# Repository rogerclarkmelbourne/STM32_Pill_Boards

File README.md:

# STM32_Pill_Boards

This repo contains a KiCad conversion of the STM32STAMP board and also two new BluePill F4 boards designed by @racemaniac and @Squonk42

My previous attemps have been deleted.

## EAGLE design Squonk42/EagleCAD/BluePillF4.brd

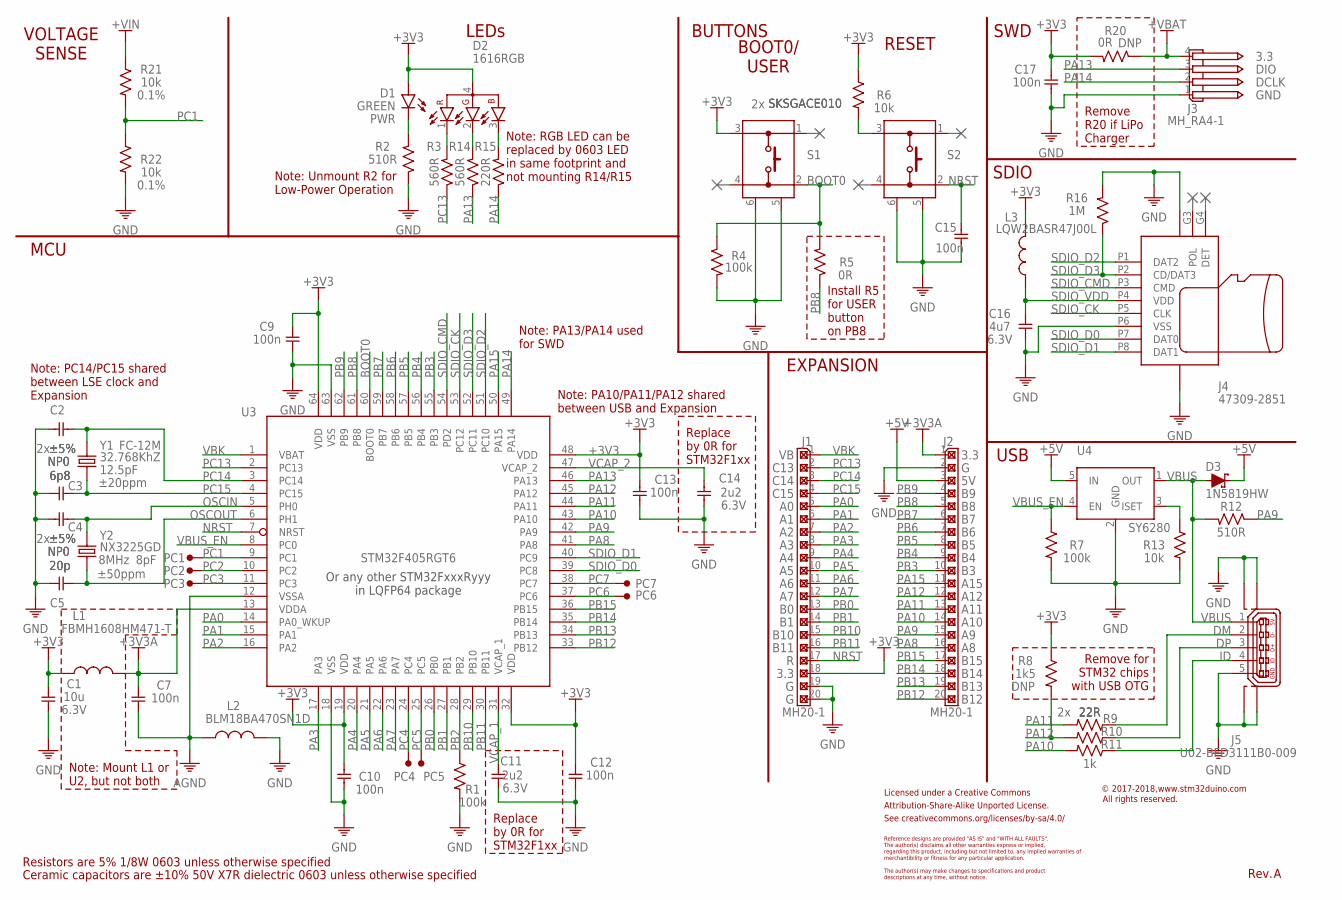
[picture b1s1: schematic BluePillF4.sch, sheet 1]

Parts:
C1: 10u; C0603; PARTNO C0603_10u_X7R_10%_CER_6V3
C2, C3: 6p8; C0603; PARTNO C0603_6p8_NP0_5%_CER_50V
C4, C5: 20p; C0603; PARTNO C0603_20p_NP0_5%_CER_50V
C7, C9, C10, C12, C13, C15, C17: 100n; C0603; PARTNO C0603_100n_X7R_10%_CER_50V
C11, C14: 2u2; C0603; PARTNO C0603_2u2_X7R_10%_CER_6V3
C16: 4u7; C0603; PARTNO C0603_4u7_X7R_10%_CER_6V3
D1: GREEN; LED0603; PARTNO LED0603-GREEN
D2: 1616RGB; PARTNO LED1616-RGB
D3: 1N5819HW; SOD-123
J1, J2: MH20-1; MH20-1-0.1; PARTNO MH20-1-0.1
J3: MH_RA4-1; MH_RA4-1-0.1; PARTNO MH_RA4-1-0.1
J4: 47309-2851
J5: U02-BFD3111B0-009; PARTNO U02-BFD3111B0-009
L1: FBMH1608HM471-T; FB0603; PARTNO FBMH1608HM471-T
L2: BLM18BA470SN1D; FB0603; PARTNO BLM18BA470SN1D
L3: LQW2BASR47J00L; FB0805; PARTNO LQW2BASR47J00L
LOGO1: CC-BY-SA_LOGO
PC1, PC2, PC3, PC4, PC5, PC6, PC7: TEST_PAD
R1, R4, R7: 100k; R0603; PARTNO R0603_100k_5%_125mW
R2, R12: 510R; R0603; PARTNO R0603_510R_5%_125mW
R3, R14: 560R; R0603; PARTNO R0603_510R_5%_125mW
R5, R20: 0R; R0603; PARTNO R0603_510R_5%_125mW
R6, R13: 10k; R0603; PARTNO R0603_10k_5%_125mW
R8: 1k5; R0603; PARTNO R0603_1k5_5%_125mW
R9, R10: 22R; R0603; PARTNO R0603_22R_5%_125mW
R11: 1k; R0603; PARTNO R0603_1k_5%_125mW
R15: 220R; R0603; PARTNO R0603_510R_5%_125mW
R16: 1M; R0603; PARTNO R0603_1M_5%_125mW
R21, R22: 10k; R0603; PARTNO R0603_10k_0.1%_125mW
S1, S2: SKSGACE010
U3: STM32F405RGT6; LQFP64
U4: SY6280; SOT23-5
Y1: FC-12M; PARTNO FC-12M 32.7680KA-A3
Y2: NX3225GD; CRYSTAL_32X25_2P; PARTNO NX3225GD-8MHZ-STD-CRA-3

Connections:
+3V3: C1.1, C9.2, C10.2, C12.1, C13.1, C17.2, D1.2 (A), D2.4 (A), J1.18, L1.1, L3.2, R6.1, R8.1, R20.2, S1.3 (A), U3.19 (VDD), U3.32 (VDD), U3.48 (VDD), U3.64 (VDD); also elsewhere on the board
+3V3A: C7.2, J2.1, L1.2, U3.13 (VDDA); also elsewhere on the board
+5V: D3.C, J2.3, U4.5 (IN); also elsewhere on the board
+VBAT: J3.4, R20.1; also elsewhere on the board
+VIN: R21.1; also elsewhere on the board
AGND: C7.1, L2.1, U3.12 (VSSA); also elsewhere on the board
BOOT0: R4.1, R5.2, S1.2 (B), U3.60 (BOOT0)
D1: D1.1 (C), R2.2
D2_B: D2.3 (CB), R15.2
D2_G: D2.2 (CG), R14.2
D2_R: D2.1 (CR), R3.2
DM: J5.2, R9.1
DP: J5.3, R10.1
GND: C1.2, C2.2, C3.2, C4.2, C5.2, C9.1, C10.1, C11.1, C12.2, C13.2, C14.1, C15.1, C16.1, C17.1, J1.19, J1.20, J2.2, J3.1, J4.G1 (GND), J4.G2 (GND), J4.P6 (VSS), J5.5, J5.S$1 (M0), J5.S$2 (M1), J5.S$3 (M2), J5.S$4 (M3), L2.2, R1.2, R2.1, R4.2, R7.2, R13.2, R16.2, R22.2, S1.5, S1.6, S2.5, S2.6, U3.18 (VSS), U3.63 (VSS), U4.2 (GND); also elsewhere on the board
ID: J5.4, R11.1
ISET: R13.1, U4.3 (ISET)
NRST: C15.2, J1.17, S2.2 (B), U3.7 (NRST)
OSCIN: C4.1, U3.5 (PH0), Y2.2
OSCOUT: C5.1, U3.6 (PH1), Y2.1
PA0: J1.5, U3.14 (PA0_WKUP)
PA1: J1.6, U3.15 (PA1)
PA2: J1.7, U3.16 (PA2)
PA3: J1.8, U3.17 (PA3)
PA4: J1.9, U3.20 (PA4)
PA5: J1.10, U3.21 (PA5)
PA6: J1.11, U3.22 (PA6)
PA7: J1.12, U3.23 (PA7)
PA8: J2.16, U3.41 (PA8)
PA9: J2.15, R12.1, U3.42 (PA9)
PA10: J2.14, R11.2, U3.43 (PA10)
PA11: J2.13, R9.2, U3.44 (PA11)
PA12: J2.12, R8.2, R10.2, U3.45 (PA12)
PA13: J3.3, R14.1, U3.46 (PA13)
PA14: J3.2, R15.1, U3.49 (PA14)
PA15: J2.11, U3.50 (PA15)
PB0: J1.13, U3.26 (PB0)
PB1: J1.14, U3.27 (PB1)
PB2: R1.1, U3.28 (PB2)
PB3: J2.10, U3.55 (PB3)
PB4: J2.9, U3.56 (PB4)
PB5: J2.8, U3.57 (PB5)
PB6: J2.7, U3.58 (PB6)
PB7: J2.6, U3.59 (PB7)
PB8: J2.5, R5.1, U3.61 (PB8)
PB9: J2.4, U3.62 (PB9)
PB10: J1.15, U3.29 (PB10)
PB11: J1.16, U3.30 (PB11)
PB12: J2.20, U3.33 (PB12)
PB13: J2.19, U3.34 (PB13)
PB14: J2.18, U3.35 (PB14)
PB15: J2.17, U3.36 (PB15)
PC1: PC1.1, R21.2, R22.1, U3.9 (PC1)
PC2: PC2.1, U3.10 (PC2)
PC3: PC3.1, U3.11 (PC3)
PC4: PC4.1, U3.24 (PC4)
PC5: PC5.1, U3.25 (PC5)
PC6: PC6.1, U3.37 (PC6)
PC7: PC7.1, U3.38 (PC7)
PC13: J1.2, R3.1, U3.2 (PC13)
PC14: C2.1, J1.3, U3.3 (PC14), Y1.2
PC15: C3.1, J1.4, U3.4 (PC15), Y1.1
R6: R6.2, S2.3 (A)
SDIO_CK: J4.P5 (CLK), U3.53 (PC12)
SDIO_CMD: J4.P3 (CMD), U3.54 (PD2)
SDIO_D0: J4.P7 (DAT0), U3.39 (PC8)
SDIO_D1: J4.P8 (DAT1), U3.40 (PC9)
SDIO_D2: J4.P1 (DAT2), U3.51 (PC10)
SDIO_D3: J4.P2 (CD/DAT3), R16.1, U3.52 (PC11)
SDIO_VDD: C16.2, J4.P4 (VDD), L3.1
VBK: J1.1, U3.1 (VBAT)
VBUS: D3.A, J5.1, R12.2, U4.1 (OUT)
VBUS_EN: R7.1, U3.8 (PC0), U4.4 (EN)
VCAP_1: C11.2, U3.31 (VCAP_1)
VCAP_2: C14.2, U3.47 (VCAP_2)

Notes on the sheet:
Licensed under a Creative Commons
Attribution-Share-Alike Unported License.
See creativecommons.org/licenses/by-sa/4.0/
Reference designs are provided "AS IS" and "WITH ALL FAULTS".
regarding this product, including but not limited to, any implied warranties of
The author(s) may make changes to specifications and product
The author(s) disclaims all other warranties express or implied,
merchantibility or fitness for any particular application.
descriptions at any time, without notice.
All rights reserved.
Rev.
Ceramic capacitors are ±10% 50V X7R dielectric 0603 unless otherwise specified
Resistors are 5% 1/8W 0603 unless otherwise specified
© 2017-2018,
Remove for STM32 chips with USB OTG
Replace by 0R for STM32F1xx
RESET
BOOT0/ USER
SWD
USB
LEDs
Install R5 for USER button on PB8
PWR
SDIO
BUTTONS
EXPANSION
MCU
Note: PC14/PC15 shared between LSE clock and Expansion
Note: PA10/PA11/PA12 shared between USB and Expansion
Note: PA13/PA14 used for SWD
DIO
DCLK
3.3
GND
C13
C14
C15
B10
B11
A15

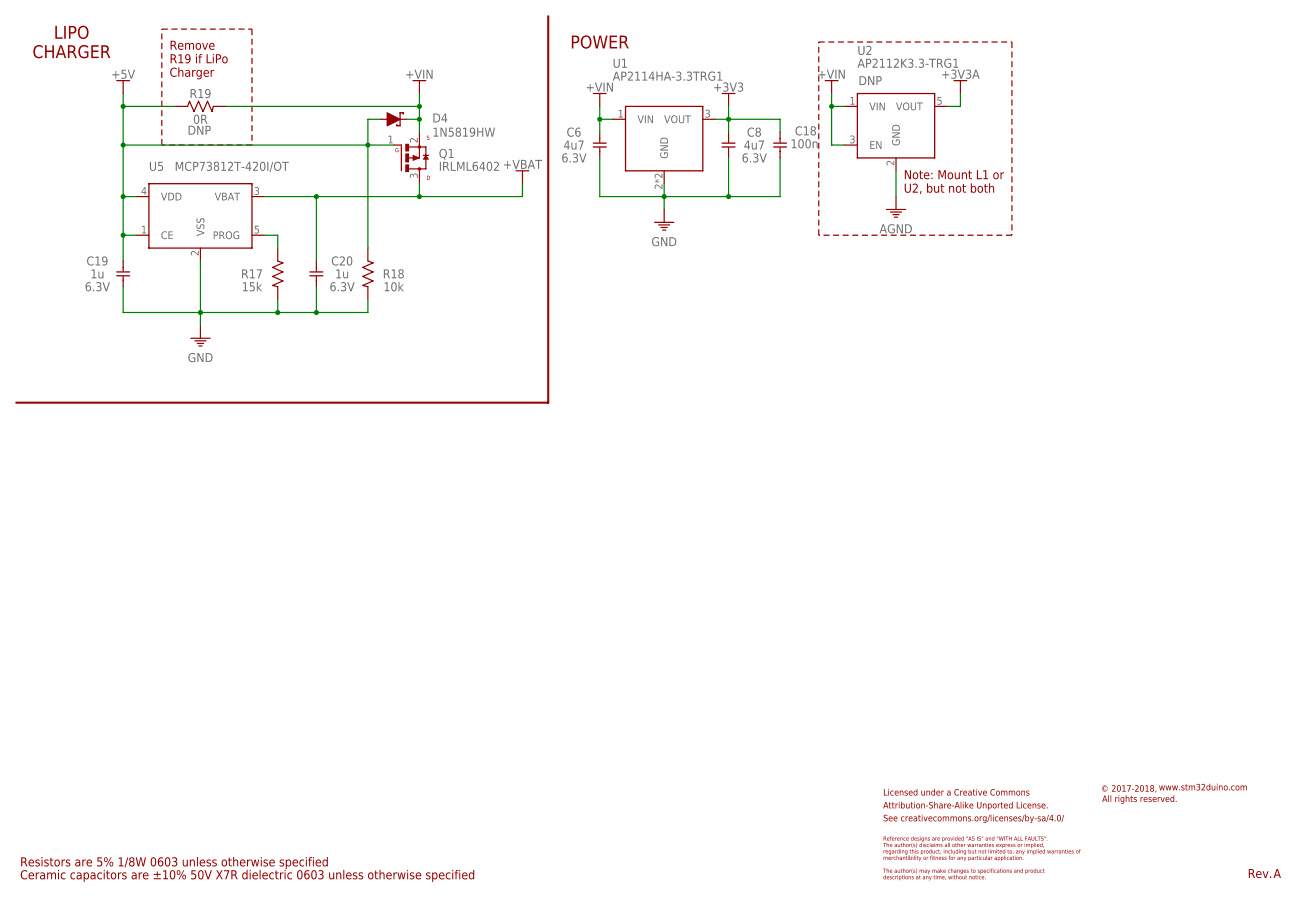
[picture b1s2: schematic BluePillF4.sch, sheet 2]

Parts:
C6, C8: 4u7; C0603; PARTNO C0603_4u7_X7R_10%_CER_6V3
C18: 100n; C0603; PARTNO C0603_100n_X7R_10%_CER_50V
C19, C20: 1u; C0603; PARTNO C0603_1u_X7R_10%_CER_6V3
D4: 1N5819HW; SOD-123
Q1: IRLML6402; SOT323
R17: 15k; R0603; PARTNO R0603_15k_5%_125mW
R18: 10k; R0603; PARTNO R0603_15k_5%_125mW
R19: 0R; R0603; PARTNO R06030R_5%_125mW
U1: AP2114HA-3.3TRG1; SOT223
U2: AP2112K3.3-TRG1; SOT23-5; PARTNO AP2112K3.3-TRG1
U5: MCP73812T-420I/OT; SOT23-5

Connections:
+3V3: C8.1, C18.1, U1.3 (VOUT); also elsewhere on the board
+3V3A: U2.5 (VOUT); also elsewhere on the board
+5V: C19.1, D4.A, Q1.1 (G), R18.1, R19.1, U5.1 (CE), U5.4 (VDD); also elsewhere on the board
+VBAT: C20.1, Q1.3 (D), U5.3 (VBAT); also elsewhere on the board
+VIN: C6.1, D4.C, Q1.2 (S), R19.2, U1.1 (VIN), U2.1 (VIN), U2.3 (EN); also elsewhere on the board
AGND: U2.2 (GND); also elsewhere on the board
GND: C6.2, C8.2, C18.2, C19.2, C20.2, R17.2, R18.2, U1.2 (GND), U1.PAD (GND), U5.2 (VSS); also elsewhere on the board
PROG: R17.1, U5.5 (PROG)

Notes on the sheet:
Licensed under a Creative Commons
Attribution-Share-Alike Unported License.
See creativecommons.org/licenses/by-sa/4.0/
Reference designs are provided "AS IS" and "WITH ALL FAULTS".
regarding this product, including but not limited to, any implied warranties of
The author(s) may make changes to specifications and product
The author(s) disclaims all other warranties express or implied,
merchantibility or fitness for any particular application.
descriptions at any time, without notice.
All rights reserved.
Rev.
Ceramic capacitors are ±10% 50V X7R dielectric 0603 unless otherwise specified
Resistors are 5% 1/8W 0603 unless otherwise specified
© 2017-2018,
LIPO CHARGER
Remove R19 if LiPo Charger
POWER
Note: Mount L1 or U2, but not both

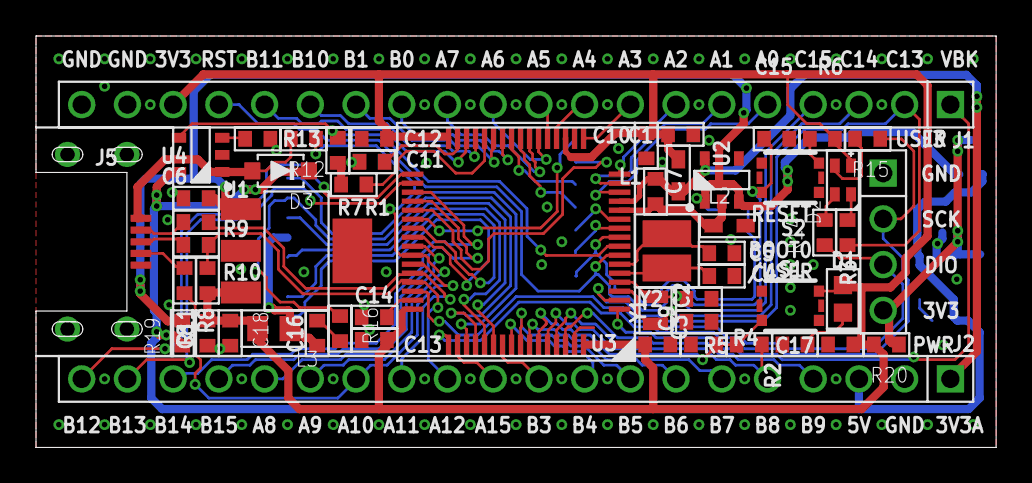
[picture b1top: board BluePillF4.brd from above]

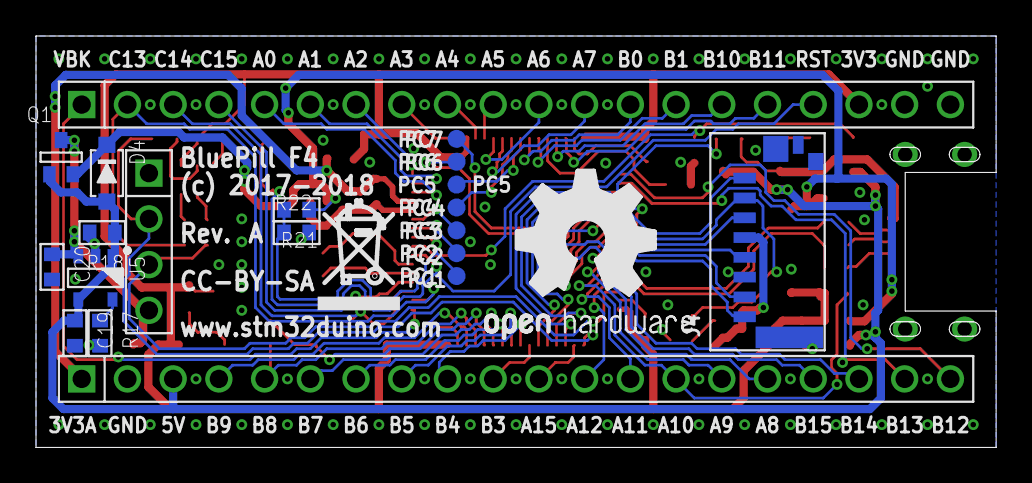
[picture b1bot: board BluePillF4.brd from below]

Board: 2 copper layers, 53.3 x 22.9 mm, 76 parts (19 on the bottom side), 75 nets.

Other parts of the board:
DRILEGEND: DRILEGEND
U$2: A5L-LOC
U$4: OPEN_HARDWARE_LOGO
U$6: RECYCLE_BIN_LOGO

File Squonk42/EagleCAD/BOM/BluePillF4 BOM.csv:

Qty-1,Part References,Value,Package,Part Num,Description,Datasheet,Digi-Key,Mouser,Aliexpress,TaoBao,XREF
1,"R5, R20(DNP)",0R,R0603,***PART# 'R0603_510R_5%_125MW' NOT FOUND***,*,*,*,*,*,*,*
0,"R19(DNP)",0R,R0603,***PART# 'R06030R_5%_125MW' NOT FOUND***,*,*,*,*,*,*,*
1,"R16",1M,R0603,***PART# 'R0603_1M_5%_125MW' NOT FOUND***,*,*,*,*,*,*,*
2,"D3, D4",1N5819HW,SOD-123,***PART# '1N5819HW' NOT FOUND***,*,*,*,*,*,*,*
1,"R11",1k,R0603,***PART# 'R0603_1K_5%_125MW' NOT FOUND***,*,*,*,*,*,*,*
0,"R8(DNP)",1k5,R0603,***PART# 'R0603_1K5_5%_125MW' NOT FOUND***,*,*,*,*,*,*,*
2,"C19, C20",1u,C0603,***PART# 'C0603_1U_X7R_10%_CER_6V3' NOT FOUND***,*,*,*,*,*,*,*
2,"C11, C14",2u2,C0603,***PART# 'C0603_2U2_X7R_10%_CER_6V3' NOT FOUND***,*,*,*,*,*,*,*
3,"C6, C8, C16",4u7,C0603,***PART# 'C0603_4U7_X7R_10%_CER_6V3' NOT FOUND***,*,*,*,*,*,*,*
2,"C2, C3",6p8,C0603,C0603_6P8_NP0_5%_CER_50V,REF9,*,*,*,*,*,*
2,"R21, R22",10k,R0603,***PART# 'R0603_10K_0.1%_125MW' NOT FOUND***,*,*,*,*,*,*,*
2,"R6, R13",10k,R0603,***PART# 'R0603_10K_5%_125MW' NOT FOUND***,*,*,*,*,*,*,*
1,"R18",10k,R0603,***PART# 'R0603_15K_5%_125MW' NOT FOUND***,*,*,*,*,*,*,*
1,"C1",10u,C0603,***PART# 'C0603_10U_X7R_10%_CER_6V3' NOT FOUND***,*,*,*,*,*,*,*
1,"R17",15k,R0603,***PART# 'R0603_15K_5%_125MW' NOT FOUND***,*,*,*,*,*,*,*
2,"C4, C5",20p,C0603,C0603_20P_NP0_5%_CER_50V,REF6,*,*,*,*,*,*
2,"R9, R10",22R,R0603,***PART# 'R0603_22R_5%_125MW' NOT FOUND***,*,*,*,*,*,*,*
3,"R1, R4, R7",100k,R0603,***PART# 'R0603_100K_5%_125MW' NOT FOUND***,*,*,*,*,*,*,*
8,"C7, C9, C10, C12, C13, C15, C17, C18",100n,C0603,C0603_100N_X7R_10%_CER_50V,REF4,*,*,*,*,*,*
5,"R15, R2, R12, R3, R14",560R,R0603,***PART# 'R0603_510R_5%_125MW' NOT FOUND***,*,*,*,*,*,*,*
1,"D2",1616RGB,1616RGB,***PART# 'LED1616-RGB' NOT FOUND***,*,*,*,*,*,*,*
1,"J4",47309-2851,47309-2851,***PART# '47309-2851' NOT FOUND***,*,*,*,*,*,*,*
0,"U2(DNP)",AP2112K3.3-TRG1,SOT23-5,***PART# 'AP2112K3.3-TRG1' NOT FOUND***,*,*,*,*,*,*,*
1,"U1",AP2114HA-3.3TRG1,SOT223,AP2114HA3.3-TRG1,REF3,*,*,*,*,*,*
1,"L2",BLM18BA470SN1D,FB0603,***PART# 'BLM18BA470SN1D' NOT FOUND***,*,*,*,*,*,*,*
1,"L1",FBMH1608HM471-T,FB0603,FBMH1608HM471-T,REF11,*,*,*,*,*,*
1,"Y1",FC-12M,FC-12M,***PART# 'FC-12M 32.7680KA-A3' NOT FOUND***,*,*,*,*,*,*,*
1,"D1",GREEN,LED0603,LED0603-GREEN,REF13,*,*,*,*,*,*
1,"Q1",IRLML6402,SOT323,***PART# 'IRLM6402' NOT FOUND***,*,*,*,*,*,*,*
1,"L3",LQW2BASR47J00L,FB0805,***PART# 'LQW2BASR47J00L' NOT FOUND***,*,*,*,*,*,*,*
1,"U5",MCP73812T-420I/OT,SOT23-5,***PART# 'MCP73812T-420I/OT' NOT FOUND***,*,*,*,*,*,*,*
2,"J1, J2",MH20-1,MH20-1-0.1,MH20-1-0.1,REF15,*,*,*,*,*,*
1,"J3",MH_RA4-1,MH_RA4-1-0.1,MH_RA4-1-0.1,REF16,*,*,*,*,*,*
1,"Y2",NX3225GD,CRYSTAL_32X25_2P,NX3225GD-8MHZ-STD-CRA-3,REF18,*,*,*,*,*,*
2,"S1, S2",SKSGACE010,SKSGACE010,SKSGACE010,REF26,*,*,*,*,*,*
1,"U3",STM32F405RGT6,LQFP64,STM32F405RGT6,REF27,*,*,*,*,*,*
1,"U4",SY6280,SOT23-5,SY6280AAC,REF28,*,*,*,*,*,*
1,"J5",U02-BFD3111B0-009,U02-BFD3111B0-009,***PART# 'U02-BFD3111B0-009' NOT FOUND***,*,*,*,*,*,*,*

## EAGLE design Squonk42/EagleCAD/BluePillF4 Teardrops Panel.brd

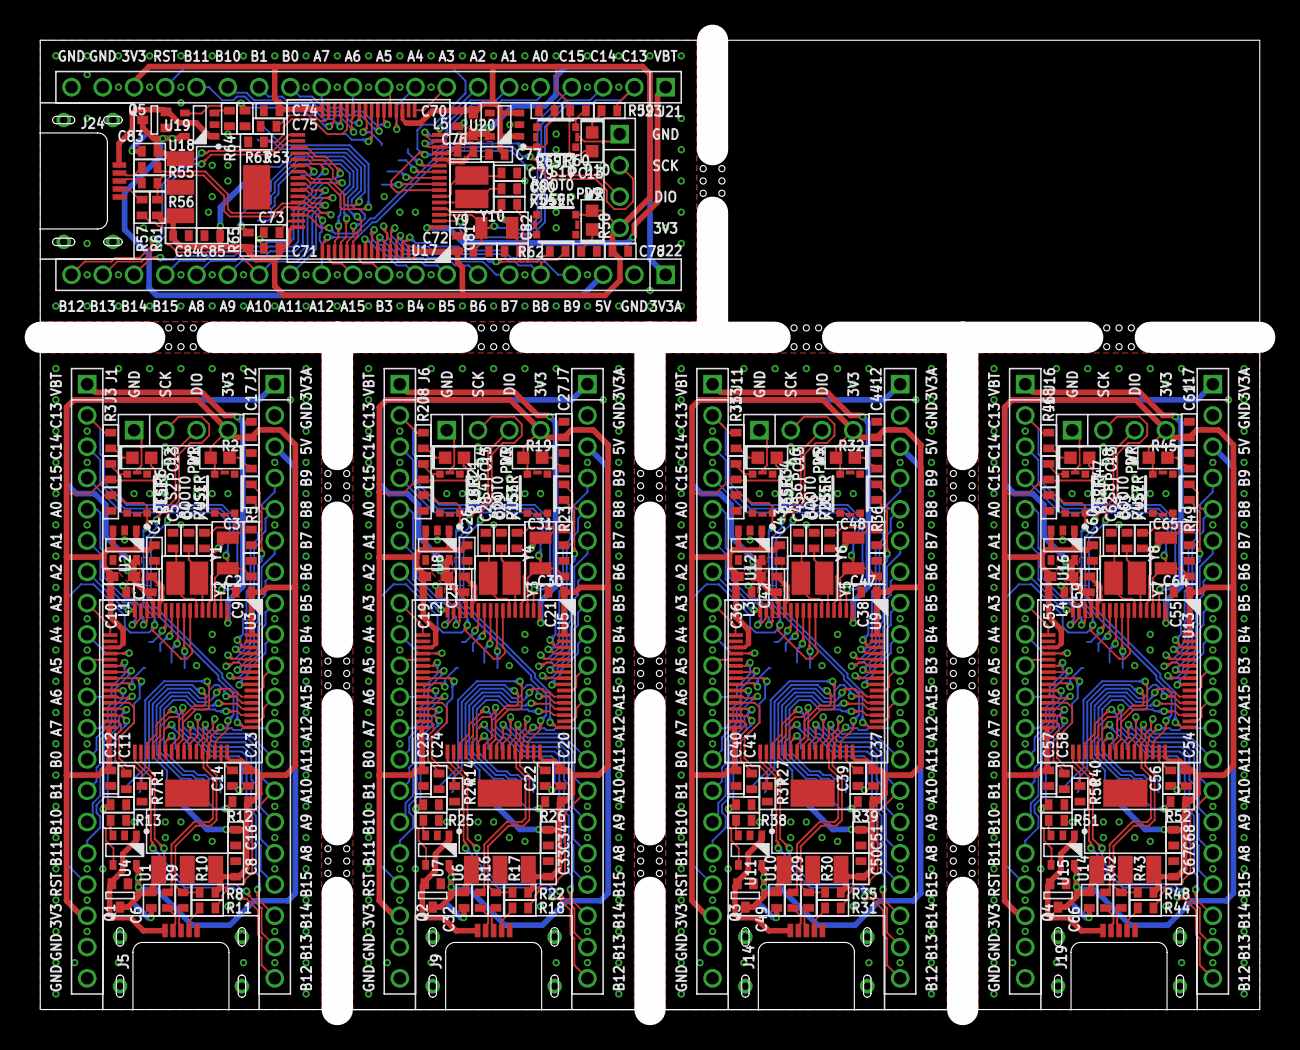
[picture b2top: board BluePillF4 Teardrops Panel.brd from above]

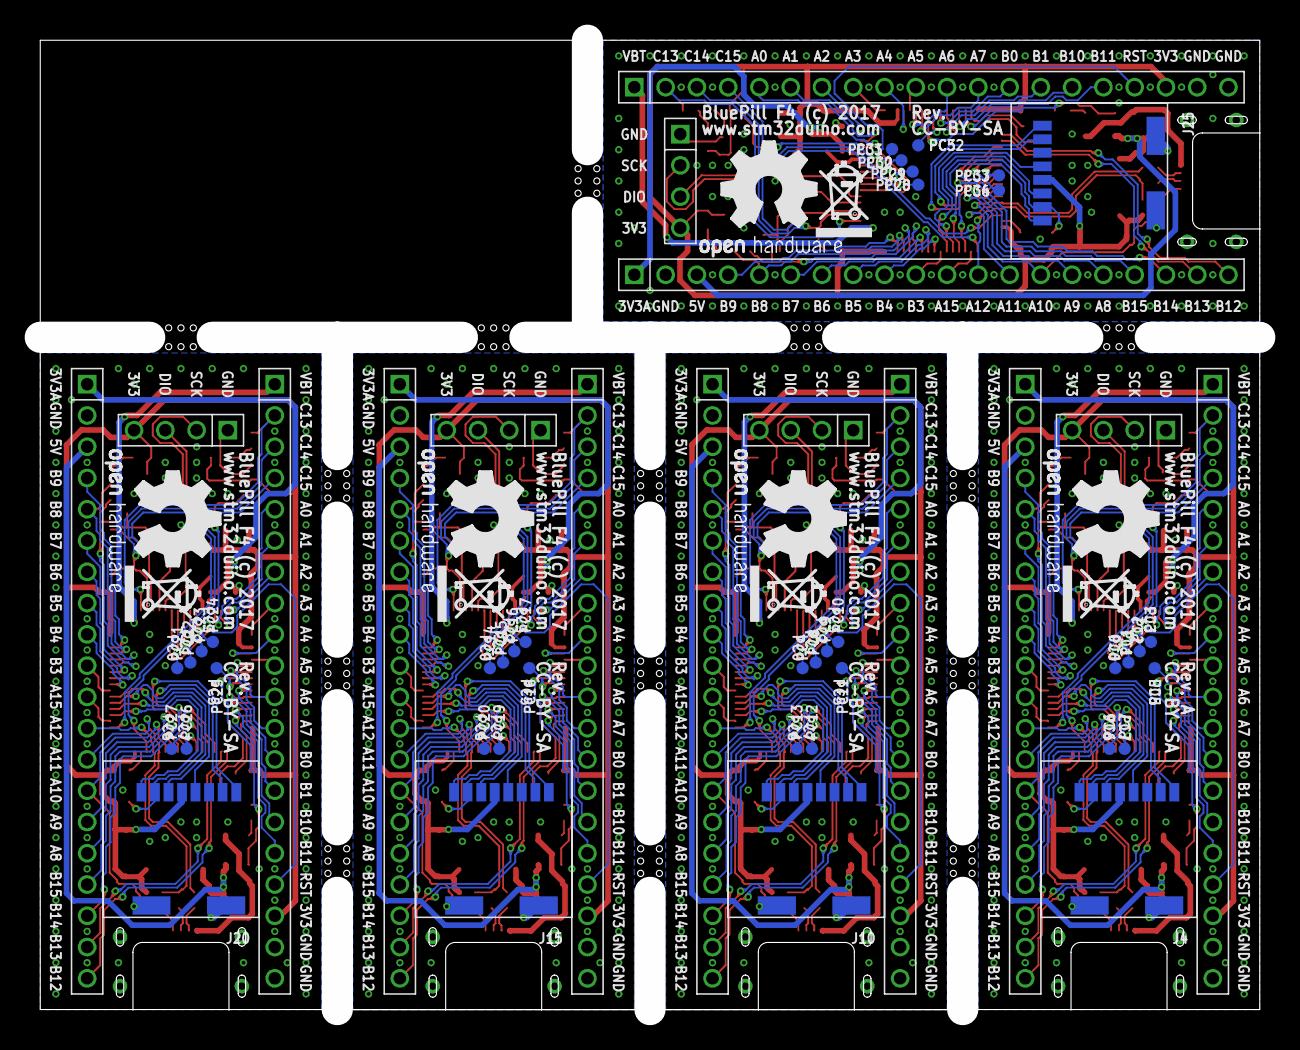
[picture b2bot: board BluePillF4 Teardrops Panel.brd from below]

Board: 2 copper layers, 99.1 x 78.7 mm, 283 parts (50 on the bottom side), 345 nets.

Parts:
C1, C26, C43, C60, C77: 10u; C0603
C2, C3, C30, C31, C47, C48, C64, C65, C81, C82: 6p8; C0603
C4, C5, C28, C29, C45, C46, C62, C63, C79, C80: 20p; C0603
C6, C8, C16, C32, C33, C34, C49, C50, C51, C66, C67, C68, C83, C84, C85: 4u7; C0603
C7, C9, C10, C12, C13, C15, C17, C18, C19, C20, C21, C23, C25, C27, C35, C36, C37, C38, C40, C42, C44, C52, C53, C54, C55, C57, C59, C61, C69, C70, C71, C72, C74, C76, C78: 100n; C0603
C11, C14, C22, C24, C39, C41, C56, C58, C73, C75: 2u2; C0603
D1, D3, D5, D7, D9: GREEN; LED0603
D2, D4, D6, D8, D10: RED; LED0603
DRILEGEND: DRILEGEND
J1, J2, J6, J7, J11, J12, J16, J17, J21, J22: MH20-1; MH20-1-0.1
J3, J8, J13, J18, J23: MH_RA4-1; MH_RA4-1-0.1
J4, J10, J15, J20, J25: MR07C-06200
J5, J9, J14, J19, J24: 47642-001; 47662-001
L1, L2, L3, L4, L5: FBMH1608HM471-T; FB0603
LOGO1: CC-BY-SA_LOGO
PC0, PC1, PC2, PC3, PC4, PC5, PC6, PC7, PC8, PC9, PC10, PC11, PC12, PC13, PC14, PC15, PC16, PC17, PC18, PC19, PC20, PC21, PC22, PC23, PC24, PC25, PC26, PC27, PC28, PC29, PC30, PC31, PC32, PC33, PC34: TEST_PAD
Q1, Q2, Q3, Q4, Q5: DMP2160UW-7; SOT323
R1, R4, R7, R12, R14, R15, R24, R26, R27, R28, R37, R39, R40, R41, R50, R52, R53, R54, R63, R65: 100k; R0603
R2, R3, R19, R20, R32, R33, R45, R46, R58, R59: 510R; R0603
R5, R23, R36, R49, R62: 0R; R0603
R6, R13, R21, R25, R34, R38, R47, R51, R60, R64: 10k; R0603
R8, R22, R35, R48, R61: 1k5; R0603
R9, R10, R16, R17, R29, R30, R42, R43, R55, R56: 22R; R0603
R11, R18, R31, R44, R57: 1k; R0603
S1, S2, S3, S4, S5, S6, S7, S8, S9, S10: SKSGACE010
U1, U6, U10, U14, U18: AP2114HA-3.3TRG1; SOT223
U2, U8, U12, U16, U20: AP2112K3.3-TRG1; SOT23-5
U3, U5, U9, U13, U17: STM32F405RGT6; LQFP64
U4, U7, U11, U15, U19: SY6280; SOT23-5
U$1, U$4, U$5, U$8, U$10: OPEN_HARDWARE_LOGO
U$2: A5L-LOC
U$3, U$6, U$7, U$9, U$11: RECYCLE_BIN_LOGO
Y1, Y4, Y6, Y8, Y10: FC-135; CRYSTAL_32X15
Y2, Y3, Y5, Y7, Y9: NX3225GD; CRYSTAL_32X25_2P

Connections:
+3V1: C19.2, C20.1, C21.2, C23.1, C26.1, C27.2, C33.1, C34.2, D3.2, D4.2, J6.18, J8.4, J10.P4, L2.1, R21.1, R22.1, R26.2, S3.3, U5.19, U5.32, U5.48, U5.64, U6.3, U8.1, U8.3
+3V2: C36.2, C37.1, C38.2, C40.1, C43.1, C44.2, C50.1, C51.2, D5.2, D6.2, J11.18, J13.4, J15.P4, L3.1, R34.1, R35.1, R39.2, S5.3, U9.19, U9.32, U9.48, U9.64, U10.3, U12.1, U12.3
+3V3: C1.1, C8.1, C9.2, C10.2, C12.1, C13.1, C16.2, C17.2, D1.2, D2.2, J1.18, J3.4, J4.P4, L1.1, R6.1, R8.1, R12.2, S1.3, U1.3, U2.1, U2.3, U3.19, U3.32, U3.48, U3.64
+3V3A: C7.2, J2.1, L1.2, U2.5, U3.13
+3V3A1: C25.2, J7.1, L2.2, U5.13, U8.5
+3V3A2: C42.2, J12.1, L3.2, U9.13, U12.5
+3V3A3: C59.2, J17.1, L4.2, U13.13, U16.5
+3V3A4: C76.2, J22.1, L5.2, U17.13, U20.5
+3V4: C53.2, C54.1, C55.2, C57.1, C60.1, C61.2, C67.1, C68.2, D7.2, D8.2, J16.18, J18.4, J20.P4, L4.1, R47.1, R48.1, R52.2, S7.3, U13.19, U13.32, U13.48, U13.64, U14.3, U16.1, U16.3
+3V5: C70.2, C71.1, C72.2, C74.1, C77.1, C78.2, C84.1, C85.2, D9.2, D10.2, J21.18, J23.4, J25.P4, L5.1, R60.1, R61.1, R65.2, S9.3, U17.19, U17.32, U17.48, U17.64, U18.3, U20.1, U20.3
+5V: C6.1, J2.3, Q1.3, U1.1, U4.5
+5V1: C32.1, J7.3, Q2.3, U6.1, U7.5
+5V2: C49.1, J12.3, Q3.3, U10.1, U11.5
+5V3: C66.1, J17.3, Q4.3, U14.1, U15.5
+5V4: C83.1, J22.3, Q5.3, U18.1, U19.5
AGND: C1.2, C7.1, U3.12
AGND1: C25.1, C26.2, U5.12
AGND2: C42.1, C43.2, U9.12
AGND3: C59.1, C60.2, U13.12
AGND4: C76.1, C77.2, U17.12
BOOT0: R4.1, R5.2, S1.2, U3.60
BOOT1: R15.1, R23.2, S3.2, U5.60
BOOT2: R28.1, R36.2, S5.2, U9.60
BOOT3: R41.1, R49.2, S7.2, U13.60
BOOT4: R54.1, R62.2, S9.2, U17.60
D1: D1.1, R2.2
D2: D2.1, R3.2
D3: D3.1, R19.2
D4: D4.1, R20.2
D5: D5.1, R32.2
D6: D6.1, R33.2
D7: D7.1, R45.2
D8: D8.1, R46.2
D9: D9.1, R58.2
D10: D10.1, R59.2
DM: J5.2, R9.1
DM1: J9.2, R16.1
DM2: J14.2, R29.1
DM3: J19.2, R42.1
DM4: J24.2, R55.1
DP: J5.3, R10.1
DP1: J9.3, R17.1
DP2: J14.3, R30.1
DP3: J19.3, R43.1
DP4: J24.3, R56.1
GND: C2.2, C3.2, C4.2, C5.2, C6.2, C8.2, C9.1, C10.1, C11.1, C12.2, C13.2, C14.1, C15.1, C16.1, C17.1, J1.19, J1.20, J2.2, J3.1, J4.G1, J4.G2, J4.P6, J5.5, J5.S$1, J5.S$2, J5.S$3, J5.S$4, Q1.1, R1.2, R2.1, R4.2, R7.2, R13.2, S1.5, S1.6, S2.5, S2.6, U1.2, U1.PAD, U2.2, U3.18, U3.63, U4.2
GND1: C18.1, C19.1, C20.2, C21.1, C22.1, C23.2, C24.1, C27.1, C28.2, C29.2, C30.2, C31.2, C32.2, C33.2, C34.1, J6.19, J6.20, J7.2, J8.1, J9.5, J9.S$1, J9.S$2, J9.S$3, J9.S$4, J10.G1, J10.G2, J10.P6, Q2.1, R14.2, R15.2, R19.1, R24.2, R25.2, S3.5, S3.6, S4.5, S4.6, U5.18, U5.63, U6.2, U6.PAD, U7.2, U8.2
GND2: C35.1, C36.1, C37.2, C38.1, C39.1, C40.2, C41.1, C44.1, C45.2, C46.2, C47.2, C48.2, C49.2, C50.2, C51.1, J11.19, J11.20, J12.2, J13.1, J14.5, J14.S$1, J14.S$2, J14.S$3, J14.S$4, J15.G1, J15.G2, J15.P6, Q3.1, R27.2, R28.2, R32.1, R37.2, R38.2, S5.5, S5.6, S6.5, S6.6, U9.18, U9.63, U10.2, U10.PAD, U11.2, U12.2
GND3: C52.1, C53.1, C54.2, C55.1, C56.1, C57.2, C58.1, C61.1, C62.2, C63.2, C64.2, C65.2, C66.2, C67.2, C68.1, J16.19, J16.20, J17.2, J18.1, J19.5, J19.S$1, J19.S$2, J19.S$3, J19.S$4, J20.G1, J20.G2, J20.P6, Q4.1, R40.2, R41.2, R45.1, R50.2, R51.2, S7.5, S7.6, S8.5, S8.6, U13.18, U13.63, U14.2, U14.PAD, U15.2, U16.2
GND4: C69.1, C70.1, C71.2, C72.1, C73.1, C74.2, C75.1, C78.1, C79.2, C80.2, C81.2, C82.2, C83.2, C84.2, C85.1, J21.19, J21.20, J22.2, J23.1, J24.5, J24.S$1, J24.S$2, J24.S$3, J24.S$4, J25.G1, J25.G2, J25.P6, Q5.1, R53.2, R54.2, R58.1, R63.2, R64.2, S9.5, S9.6, S10.5, S10.6, U17.18, U17.63, U18.2, U18.PAD, U19.2, U20.2
ID: J5.4, R11.1
ID1: J9.4, R18.1
ID2: J14.4, R31.1
ID3: J19.4, R44.1
ID4: J24.4, R57.1
ISET: R13.1, U4.3
ISET1: R25.1, U7.3
ISET2: R38.1, U11.3
ISET3: R51.1, U15.3
ISET4: R64.1, U19.3
NRST: C15.2, J1.17, S2.2, U3.7
NRST1: C18.2, J6.17, S4.2, U5.7
NRST2: C35.2, J11.17, S6.2, U9.7
NRST3: C52.2, J16.17, S8.2, U13.7
NRST4: C69.2, J21.17, S10.2, U17.7
OSCIN: C4.1, U3.5, Y2.2
OSCIN1: C29.1, U5.5, Y3.2
OSCIN2: C46.1, U9.5, Y5.2
OSCIN3: C63.1, U13.5, Y7.2
OSCIN4: C80.1, U17.5, Y9.2
OSCOUT: C5.1, U3.6, Y2.1
OSCOUT1: C28.1, U5.6, Y3.1
OSCOUT2: C45.1, U9.6, Y5.1
OSCOUT3: C62.1, U13.6, Y7.1
OSCOUT4: C79.1, U17.6, Y9.1
PA0: J1.5, U3.14
PA1: J1.6, U3.15
PA2: J1.7, U3.16
PA3: J1.8, U3.17
PA4: J1.9, U3.20
PA5: J1.10, U3.21
PA6: J1.11, U3.22
PA7: J1.12, U3.23
PA8: J2.16, U3.41
PA9: J2.15, U3.42
PA10: J2.14, R11.2, U3.43
PA11: J2.13, R9.2, U3.44
PA12: J2.12, R8.2, R10.2, U3.45
PA13: J3.3, U3.46
PA14: J3.2, U3.49
PA15: J2.11, U3.50
PA16: J6.5, U5.14
PA17: J6.6, U5.15
PA18: J6.7, U5.16
PA19: J6.8, U5.17
PA20: J6.9, U5.20
PA21: J6.10, U5.21
PA22: J6.11, U5.22
PA23: J6.12, U5.23
PA24: J8.3, U5.46
PA25: J7.12, R17.2, R22.2, U5.45
PA26: J7.13, R16.2, U5.44
PA27: J7.14, R18.2, U5.43
PA28: J7.15, U5.42
PA29: J7.16, U5.41
PA30: J7.11, U5.50
PA31: J8.2, U5.49
PA32: J11.5, U9.14
PA33: J11.6, U9.15
PA34: J11.7, U9.16
PA35: J11.8, U9.17
PA36: J11.9, U9.20
PA37: J11.10, U9.21
PA38: J11.11, U9.22
PA39: J11.12, U9.23
PA40: J13.3, U9.46
PA41: J12.12, R30.2, R35.2, U9.45
PA42: J12.13, R29.2, U9.44
PA43: J12.14, R31.2, U9.43
PA44: J12.15, U9.42
PA45: J12.16, U9.41
PA46: J12.11, U9.50
PA47: J13.2, U9.49
PA48: J16.5, U13.14
PA49: J16.6, U13.15
PA50: J16.7, U13.16
PA51: J16.8, U13.17
PA52: J16.9, U13.20
PA53: J16.10, U13.21
PA54: J16.11, U13.22
PA55: J16.12, U13.23
PA56: J18.3, U13.46
PA57: J17.12, R43.2, R48.2, U13.45
PA58: J17.13, R42.2, U13.44
PA59: J17.14, R44.2, U13.43
PA60: J17.15, U13.42
PA61: J17.16, U13.41
PA62: J17.11, U13.50
PA63: J18.2, U13.49
PA64: J21.5, U17.14
PA65: J21.6, U17.15
PA66: J21.7, U17.16
PA67: J21.8, U17.17
PA68: J21.9, U17.20
PA69: J21.10, U17.21
PA70: J21.11, U17.22
PA71: J21.12, U17.23
PA72: J23.3, U17.46
PA73: J22.12, R56.2, R61.2, U17.45
PA74: J22.13, R55.2, U17.44
PA75: J22.14, R57.2, U17.43
PA76: J22.15, U17.42
PA77: J22.16, U17.41
PA78: J22.11, U17.50
PA79: J23.2, U17.49
PB0: J1.13, U3.26
PB1: J1.14, U3.27
PB2: R1.1, U3.28
PB3: J2.10, U3.55
PB4: J2.9, U3.56
PB5: J2.8, U3.57
PB6: J2.7, U3.58
PB7: J2.6, U3.59
PB8: J2.5, R5.1, U3.61
PB9: J2.4, U3.62
PB10: J1.15, U3.29
PB11: J1.16, U3.30
PB12: J2.20, U3.33
PB13: J2.19, U3.34
PB14: J2.18, U3.35
PB15: J2.17, U3.36
PB16: J6.13, U5.26
PB17: J6.14, U5.27
PB18: R14.1, U5.28
PB19: J6.15, U5.29
PB20: J6.16, U5.30
PB21: J7.17, U5.36
PB22: J7.18, U5.35
PB23: J7.19, U5.34
PB24: J7.20, U5.33
PB25: J7.4, U5.62
PB26: J7.5, R23.1, U5.61
PB27: J7.6, U5.59
PB28: J7.7, U5.58
PB29: J7.8, U5.57
PB30: J7.9, U5.56
PB31: J7.10, U5.55
PB32: J11.13, U9.26
PB33: J11.14, U9.27
PB34: R27.1, U9.28
PB35: J11.15, U9.29
PB36: J11.16, U9.30
PB37: J12.17, U9.36
PB38: J12.18, U9.35
PB39: J12.19, U9.34
PB40: J12.20, U9.33
PB41: J12.4, U9.62
PB42: J12.5, R36.1, U9.61
PB43: J12.6, U9.59
PB44: J12.7, U9.58
PB45: J12.8, U9.57
PB46: J12.9, U9.56
PB47: J12.10, U9.55
PB48: J16.13, U13.26
PB49: J16.14, U13.27
PB50: R40.1, U13.28
PB51: J16.15, U13.29
PB52: J16.16, U13.30
PB53: J17.17, U13.36
PB54: J17.18, U13.35
PB55: J17.19, U13.34
PB56: J17.20, U13.33
PB57: J17.4, U13.62
PB58: J17.5, R49.1, U13.61
PB59: J17.6, U13.59
PB60: J17.7, U13.58
PB61: J17.8, U13.57
PB62: J17.9, U13.56
PB63: J17.10, U13.55
PB64: J21.13, U17.26
PB65: J21.14, U17.27
PB66: R53.1, U17.28
PB67: J21.15, U17.29
PB68: J21.16, U17.30
PB69: J22.17, U17.36
PB70: J22.18, U17.35
PB71: J22.19, U17.34
PB72: J22.20, U17.33
PB73: J22.4, U17.62
PB74: J22.5, R62.1, U17.61
PB75: J22.6, U17.59
PB76: J22.7, U17.58
PB77: J22.8, U17.57
PB78: J22.9, U17.56
PB79: J22.10, U17.55
PC0: PC0.1, U3.8
PC1: PC1.1, U3.9
PC2: PC2.1, U3.10
PC3: PC3.1, U3.11
PC4: J6.2, R20.1, U5.2
PC5: PC5.1, U3.25
PC6: PC6.1, U3.37
PC7: PC7.1, U3.38
PC8: C30.1, J6.3, U5.3, Y4.2
PC9: C31.1, J6.4, U5.4, Y4.1
PC10: PC4.1, U5.8
PC11: PC8.1, U5.9
PC12: PC9.1, U5.10
PC13: J1.2, R3.1, U3.2
PC14: C2.1, J1.3, U3.3, Y1.2
PC15: C3.1, J1.4, U3.4, Y1.1
PC16: PC10.1, U5.11
PC17: PC11.1, U5.25
PC18: PC12.1, U5.38
PC19: PC13.1, U5.37
PC20: J11.2, R33.1, U9.2
PC21: C47.1, J11.3, U9.3, Y6.2
PC22: C48.1, J11.4, U9.4, Y6.1
PC23: PC14.1, U9.8
PC24: PC15.1, U9.9
PC25: PC16.1, U9.10
PC26: PC17.1, U9.11
PC27: PC18.1, U9.25
PC28: PC19.1, U9.38
PC29: PC20.1, U9.37
PC30: J16.2, R46.1, U13.2
PC31: C64.1, J16.3, U13.3, Y8.2
PC32: C65.1, J16.4, U13.4, Y8.1
PC33: PC21.1, U13.8
PC34: PC22.1, U13.9
PC35: PC23.1, U13.10
PC36: PC24.1, U13.11
PC37: PC25.1, U13.25
PC38: PC26.1, U13.38
PC39: PC27.1, U13.37
PC40: J21.2, R59.1, U17.2
PC41: C81.1, J21.3, U17.3, Y10.2
PC42: C82.1, J21.4, U17.4, Y10.1
PC43: PC28.1, U17.8
PC44: PC29.1, U17.9
PC45: PC30.1, U17.10
PC46: PC31.1, U17.11
PC47: PC32.1, U17.25
PC48: PC33.1, U17.38
PC49: PC34.1, U17.37
R1: R21.2, S4.3
R2: R34.2, S6.3
R3: R47.2, S8.3
R4: R60.2, S10.3
R6: R6.2, S2.3
SDIO_CK: J4.P5, U3.53
SDIO_CK1: J10.P5, U5.53
SDIO_CK2: J15.P5, U9.53
SDIO_CK3: J20.P5, U13.53
SDIO_CK4: J25.P5, U17.53
SDIO_CMD: J4.P3, U3.54
SDIO_CMD1: J10.P3, U5.54
SDIO_CMD2: J15.P3, U9.54
SDIO_CMD3: J20.P3, U13.54
SDIO_CMD4: J25.P3, U17.54
SDIO_D0: J4.P7, U3.39
SDIO_D1: J4.P8, U3.40
SDIO_D2: J4.P1, U3.51
SDIO_D3: J4.P2, R12.1, U3.52
SDIO_D4: J10.P2, R26.1, U5.52
SDIO_D5: J10.P1, U5.51
SDIO_D6: J10.P8, U5.40
SDIO_D7: J10.P7, U5.39
SDIO_D8: J15.P2, R39.1, U9.52
SDIO_D9: J15.P1, U9.51
SDIO_D10: J15.P8, U9.40
SDIO_D11: J15.P7, U9.39
SDIO_D12: J20.P2, R52.1, U13.52
SDIO_D13: J20.P1, U13.51
SDIO_D14: J20.P8, U13.40
SDIO_D15: J20.P7, U13.39
SDIO_D16: J25.P2, R65.1, U17.52
SDIO_D17: J25.P1, U17.51
SDIO_D18: J25.P8, U17.40
SDIO_D19: J25.P7, U17.39
VBAT: J1.1, U3.1
VBAT1: J6.1, U5.1
VBAT2: J11.1, U9.1
VBAT3: J16.1, U13.1
VBAT4: J21.1, U17.1
VBUS: J5.1, Q1.2, U4.1
VBUS1: J9.1, Q2.2, U7.1
VBUS2: J14.1, Q3.2, U11.1
VBUS3: J19.1, Q4.2, U15.1
VBUS4: J24.1, Q5.2, U19.1
VBUS_EN: R7.1, U3.24, U4.4
VBUS_EN1: R24.1, U5.24, U7.4
VBUS_EN2: R37.1, U9.24, U11.4
VBUS_EN3: R50.1, U13.24, U15.4
VBUS_EN4: R63.1, U17.24, U19.4
VCAP_1: C11.2, U3.31
VCAP_2: C14.2, U3.47
VCAP_3: C24.2, U5.31
VCAP_4: C22.2, U5.47
VCAP_5: C41.2, U9.31
VCAP_6: C39.2, U9.47
VCAP_7: C58.2, U13.31
VCAP_8: C56.2, U13.47
VCAP_9: C75.2, U17.31
VCAP_10: C73.2, U17.47

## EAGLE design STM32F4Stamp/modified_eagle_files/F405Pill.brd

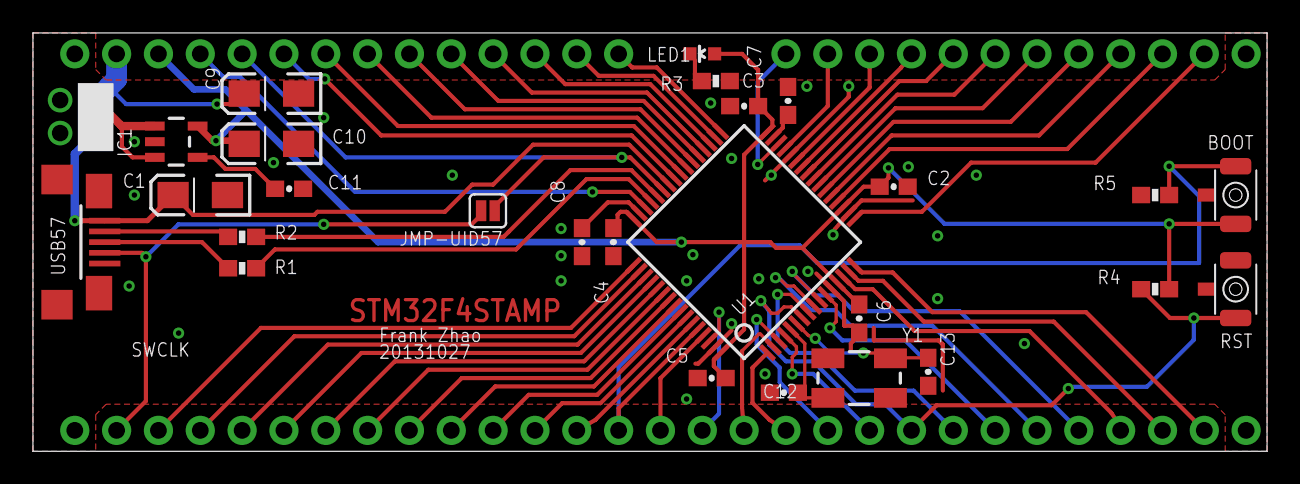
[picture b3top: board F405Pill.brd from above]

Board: 2 copper layers, 74.9 x 25.4 mm, 111 parts (0 on the bottom side), 63 nets.

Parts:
C1, C9, C10: 4u7; EIA3216-KIT
C2, C3, C4, C5, C6: 100n; 0603-CAP
C7, C8: 2u2; 0603-CAP
C11: 470p; 0603-CAP
C12, C13: 22p; 0603-CAP
IC1: VREG-3V3; SOT23-5
JMP-HOLDER57: 1X02_2MM_TH
JMP-UID57: SJ_2S
JMP-USB57: 1X02_2MM_TH
JP2: 5V; 1X1-HEADER-HOLE
JP3, JP5, JP6, JP7: GND; 1X1-HEADER-HOLE
JP4: 3V3; 1X1-HEADER-HOLE
JP8: PB8; 1X1-HEADER-HOLE
JP9: PA10; 1X1-HEADER-HOLE
JP10: PA8; 1X1-HEADER-HOLE
JP11: PA13; 1X1-HEADER-HOLE
JP12: PC9; 1X1-HEADER-HOLE
JP13: PC15; 1X1-HEADER-HOLE
JP14: PC14; 1X1-HEADER-HOLE
JP15: PC13; 1X1-HEADER-HOLE
JP16: PC12; 1X1-HEADER-HOLE
JP17: PC11; 1X1-HEADER-HOLE
JP18: PC10; 1X1-HEADER-HOLE
JP19: PC8; 1X1-HEADER-HOLE
JP20: PC7; 1X1-HEADER-HOLE
JP21: PC6; 1X1-HEADER-HOLE
JP22: PC5; 1X1-HEADER-HOLE
JP23: PC4; 1X1-HEADER-HOLE
JP24: PC3; 1X1-HEADER-HOLE
JP25: PC2; 1X1-HEADER-HOLE
JP26: PC1; 1X1-HEADER-HOLE
JP27: PC0; 1X1-HEADER-HOLE
JP28: PD2; 1X1-HEADER-HOLE
JP29: PA0; 1X1-HEADER-HOLE
JP30: PA1; 1X1-HEADER-HOLE
JP31: PA2; 1X1-HEADER-HOLE
JP32: PA3; 1X1-HEADER-HOLE
JP33: PA4; 1X1-HEADER-HOLE
JP34: PA5; 1X1-HEADER-HOLE
JP35: PA6; 1X1-HEADER-HOLE
JP36: PA7; 1X1-HEADER-HOLE
JP37: PA14; 1X1-HEADER-HOLE
JP38: PA15; 1X1-HEADER-HOLE
JP39: PB0; 1X1-HEADER-HOLE
JP40: PB1; 1X1-HEADER-HOLE
JP41: PB3; 1X1-HEADER-HOLE
JP42: PB4; 1X1-HEADER-HOLE
JP43: PB5; 1X1-HEADER-HOLE
JP44: PB6; 1X1-HEADER-HOLE
JP45: PB7; 1X1-HEADER-HOLE
JP46: PB9; 1X1-HEADER-HOLE
JP47: PB10; 1X1-HEADER-HOLE
JP48: PB11; 1X1-HEADER-HOLE
JP49: PB12; 1X1-HEADER-HOLE
JP50: PB13; 1X1-HEADER-HOLE
JP51: PB14; 1X1-HEADER-HOLE
JP52: PB15; 1X1-HEADER-HOLE
JP53: VBAT; 1X1-HEADER-HOLE
JP54: !RST; 1X1-HEADER-HOLE
JP55: BOOT0; 1X1-HEADER-HOLE
JP56: USB-ID; 1X1-HEADER-HOLE
LED1: LED-0603
R1, R2: 22R; 0603-RES
R3: 470R; 0603-RES
R4, R5: 10K; 0603-RES
SW1: !RST; SWITCH-TACT-B3U-1100P-B
SW2: BOOT; SWITCH-TACT-B3U-1100P-B
U1: STM32F405RGT; LQFP64
USB57: USB-MICROB-SMD
VP_0, VP_1, VP_2, VP_3, VP_4, VP_5, VP_6, VP_7, VP_8, VP_9, VP_10, VP_11, VP_12, VP_13, VP_14, VP_15, VP_16, VP_17, VP_18, VP_19, VP_20, VP_21, VP_22, VP_23, VP_24, VP_25, VP_26, VP_27: VPDEV0; VPAC0
Y1: 8MHz; CRYSTAL-SMD-5X3

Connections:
3.3V: C2.1, C3.1, C4.1, C5.1, C6.1, C10.A, IC1.5, JP4.1, LED1.A, R4.2, SW2.1, U1.13, U1.19, U1.32, U1.48, U1.64
5V: C9.A, IC1.1, IC1.3, JMP-USB57.2, JP2.1
GND: C1.C, C2.2, C3.2, C4.2, C5.2, C6.2, C7.2, C8.2, C9.C, C10.C, C11.1, C12.2, C13.2, IC1.2, JP3.1, JP5.1, JP6.1, JP7.1, R3.1, R5.2, SW1.2, SW1.BOSS, SW2.BOSS, U1.12, U1.18, U1.28, U1.63, USB57.GND, USB57.MT1, USB57.MT2, USB57.MT3, USB57.MT4, VP_0.VP, VP_1.VP, VP_2.VP, VP_3.VP, VP_4.VP, VP_5.VP, VP_6.VP, VP_7.VP, VP_8.VP, VP_9.VP, VP_10.VP, VP_11.VP, VP_12.VP, VP_13.VP, VP_14.VP, VP_15.VP, VP_16.VP, VP_17.VP, VP_18.VP, VP_19.VP, VP_20.VP, VP_21.VP, VP_22.VP, VP_23.VP, VP_24.VP, VP_25.VP, VP_26.VP, VP_27.VP
unnamed: R1.2, U1.45
unnamed: R2.2, U1.44
unnamed: C1.A, JMP-USB57.1, U1.42, USB57.VBUS
unnamed: JP12.1, U1.40
unnamed: R1.1, USB57.D+
unnamed: R2.1, USB57.D-
unnamed: JP8.1, U1.61
unnamed: C11.2, IC1.4
unnamed: JP10.1, U1.41
unnamed: JP11.1, U1.46
unnamed: C13.1, U1.6, Y1.1
unnamed: C7.1, U1.31
unnamed: C8.1, U1.47
unnamed: C12.1, U1.5, Y1.3
unnamed: JP55.1, R5.1, SW2.2, U1.60
unnamed: JP54.1, R4.1, SW1.1, U1.7
unnamed: LED1.C, R3.2
unnamed: JMP-UID57.2, JP56.1, USB57.ID
unnamed: JMP-UID57.1, JP9.1, U1.43
unnamed: JP13.1, U1.4
unnamed: JP14.1, U1.3
unnamed: JP15.1, U1.2
unnamed: JP16.1, U1.53
unnamed: JP17.1, U1.52
unnamed: JP18.1, U1.51
unnamed: JP19.1, U1.39
unnamed: JP20.1, U1.38
unnamed: JP21.1, U1.37
unnamed: JP22.1, U1.25
unnamed: JP23.1, U1.24
unnamed: JP24.1, U1.11
unnamed: JP25.1, U1.10
unnamed: JP26.1, U1.9
unnamed: JP27.1, U1.8
unnamed: JP28.1, U1.54
unnamed: JP29.1, U1.14
unnamed: JP30.1, U1.15
unnamed: JP31.1, U1.16
unnamed: JP32.1, U1.17
unnamed: JP33.1, U1.20
unnamed: JP34.1, U1.21
unnamed: JP35.1, U1.22
unnamed: JP36.1, U1.23
unnamed: JP37.1, U1.49
unnamed: JP38.1, U1.50
unnamed: JP39.1, U1.26
unnamed: JP40.1, U1.27
unnamed: JP41.1, U1.55
unnamed: JP42.1, U1.56
unnamed: JP43.1, U1.57
unnamed: JP44.1, U1.58
unnamed: JP45.1, U1.59
unnamed: JP46.1, U1.62
unnamed: JP47.1, U1.29
unnamed: JP48.1, U1.30
unnamed: JP49.1, U1.33
unnamed: JP50.1, U1.34
unnamed: JP51.1, U1.35
unnamed: JP52.1, U1.36
unnamed: JP53.1, U1.1

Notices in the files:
Squonk42/BluePillF4.sch:
© 2017-2018 www.stm32duino.com, All rights reserved.
Squonk42/EagleCAD/BluePillF4 Teardrops Panel.brd:
BluePill F4 (c) 2017
Squonk42/EagleCAD/BluePillF4.brd:
(c) 2017-2018
parts and their libraries:
BluePillF4: See creativecommons.org/licenses/by-sa/4.0/ for details.
BluePillF4: See creativecommons.org/licenses/by-sa/3.0/ for details.
